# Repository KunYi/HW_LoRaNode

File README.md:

Agritech with LoRa
===
the project want to make an agritech sensor baseboard.

initial version will use RS485 to connection multi-agricultural sensors for precision agriculture management requirments

---
PCB 3D-preview

---
hardward design use [KiCad EDA](https://kicad-pcb.org/)

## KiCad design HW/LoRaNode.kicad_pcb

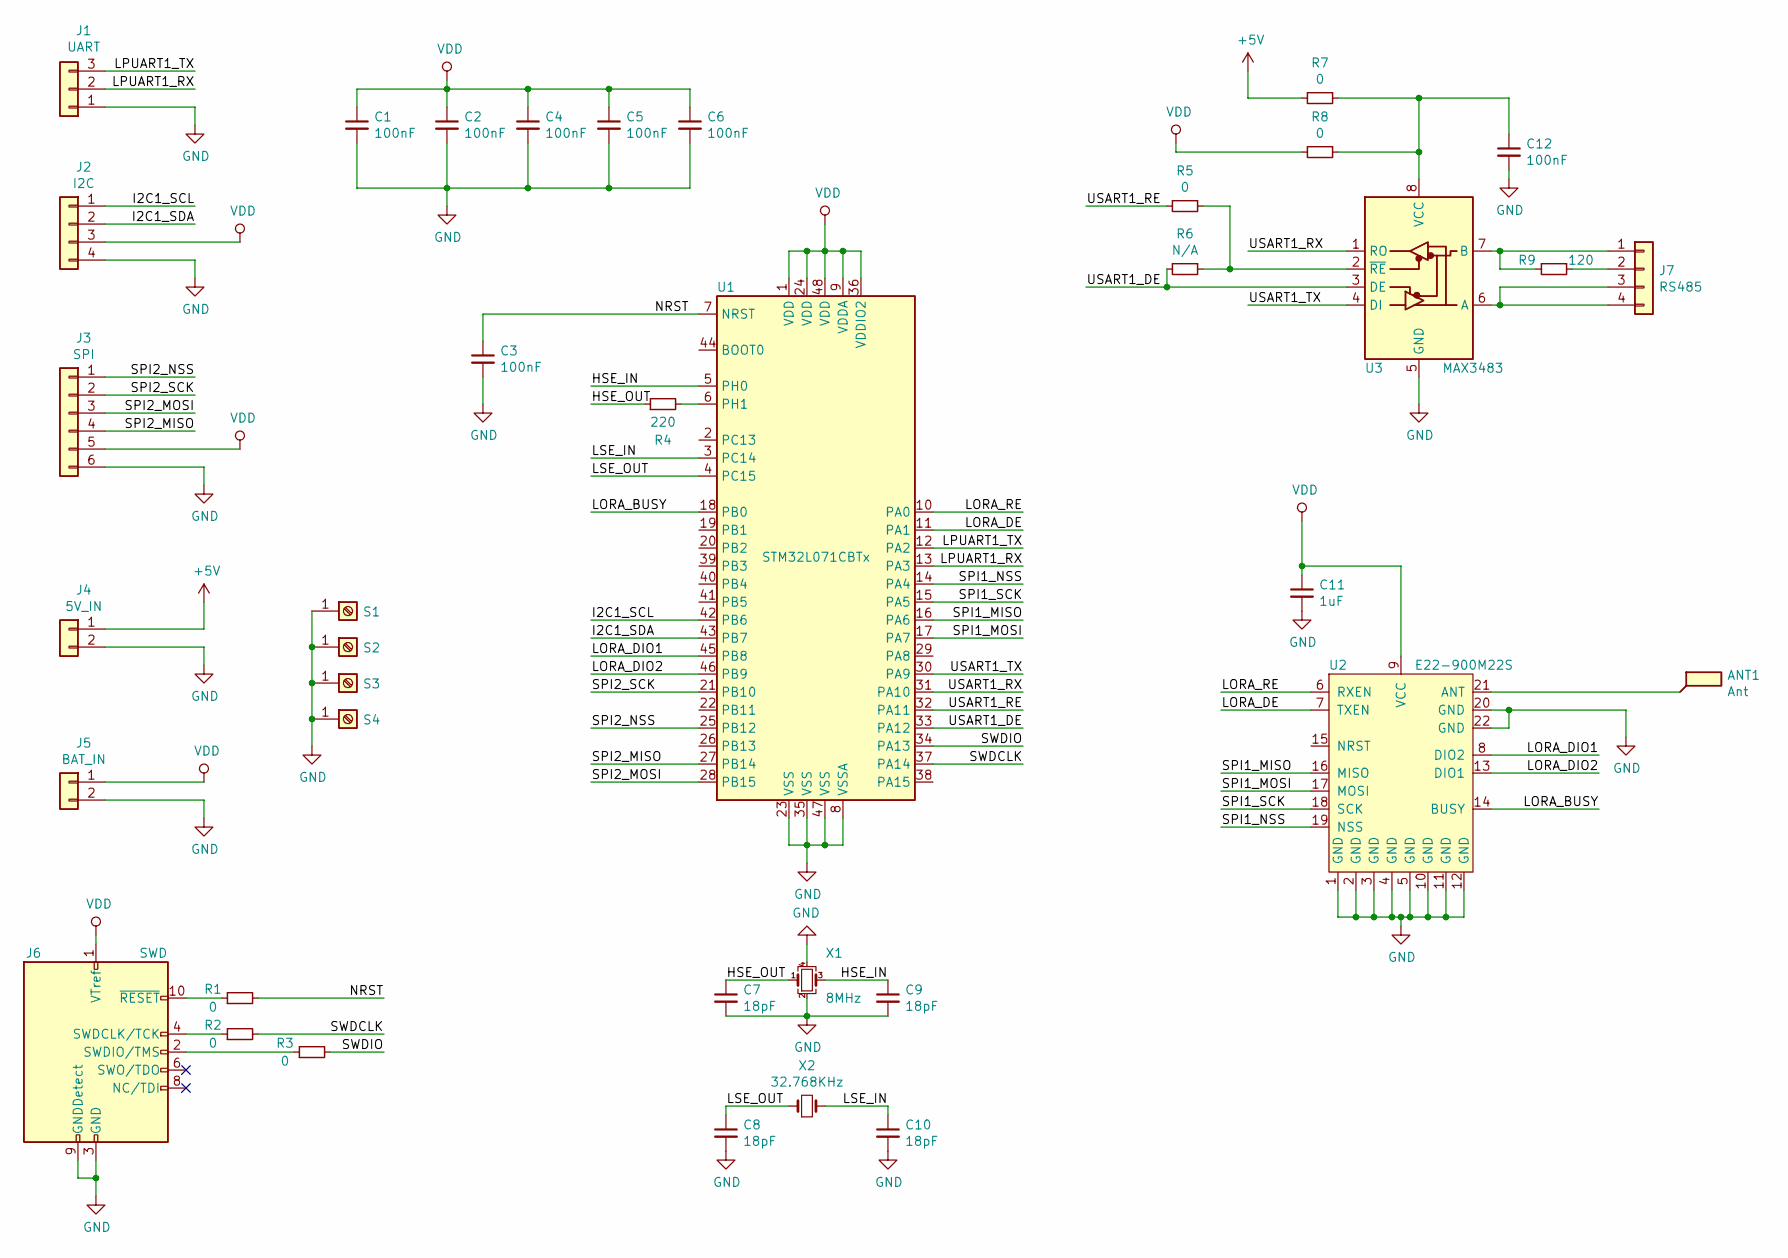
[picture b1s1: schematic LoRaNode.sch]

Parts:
ANT1: Ant; TestPoint_Pad_2.0x2.0mm
C1, C2, C3, C4, C5, C6, C12: 100nF; C_0402_1005Metric
C7, C8, C9, C10: 18pF; C_0402_1005Metric
C11: 1uF; C_0603_1608Metric
J1: UART; PinSocket_1x03_P2.00mm_Vertical
J2: I2C; PinSocket_1x04_P2.00mm_Vertical
J3: SPI; PinSocket_1x06_P2.00mm_Vertical
J4: 5V_IN; PinSocket_1x02_P2.54mm_Vertical
J5: BAT_IN; PinSocket_1x02_P2.54mm_Vertical
J6: SWD; PinHeader_2x05_P1.27mm_Vertical_SMD
J7: RS485; PinHeader_1x04_P2.54mm_Vertical
R1, R2, R3, R5, R7, R8: 0; R_0402_1005Metric
R4: 220; R_0402_1005Metric
R6: N/A; R_0402_1005Metric
R9: 120; R_0603_1608Metric
S1: S1; TestPoint_Plated_Hole_D3.0mm
S2: S2; TestPoint_Plated_Hole_D3.0mm
S3: S3; TestPoint_Plated_Hole_D3.0mm
S4: S4; TestPoint_Plated_Hole_D3.0mm
U1: STM32L071CBTx; LQFP-48_7x7mm_P0.5mm
U2: E22-900M22S; EBYTE-E22-XXXM22S
U3: MAX3483; SO-8_3.9x4.9mm_P1.27mm
X1: 8MHz; Crystal_SMD_TXC_7M-4Pin_3.2x2.5mm
X2: 32.768KHz; Crystal_SMD_3215-2Pin_3.2x1.5mm

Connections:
+5V: J4.1, R7.2
/HSE_IN: C9.1, U1.5 (PH0), X1.3
/HSE_OUT: C7.1, R4.1, X1.1
/I2C1_SCL: J2.1, U1.42 (PB6)
/I2C1_SDA: J2.2, U1.43 (PB7)
/LORA_BUSY: U1.18 (PB0), U2.14 (BUSY)
/LORA_DE: U1.11 (PA1), U2.7 (TXEN)
/LORA_DIO1: U1.45 (PB8), U2.8 (DIO2)
/LORA_DIO2: U1.46 (PB9), U2.13 (DIO1)
/LORA_RE: U1.10 (PA0), U2.6 (RXEN)
/LPUART1_RX: J1.2, U1.13 (PA3)
/LPUART1_TX: J1.3, U1.12 (PA2)
/LSE_IN: C10.1, U1.3 (PC14), X2.2
/LSE_OUT: C8.1, U1.4 (PC15), X2.1
/NRST: C3.1, R1.2, U1.7 (NRST)
/SPI1_MISO: U1.16 (PA6), U2.16 (MISO)
/SPI1_MOSI: U1.17 (PA7), U2.17 (MOSI)
/SPI1_NSS: U1.14 (PA4), U2.19 (NSS)
/SPI1_SCK: U1.15 (PA5), U2.18 (SCK)
/SPI2_MISO: J3.4, U1.27 (PB14)
/SPI2_MOSI: J3.3, U1.28 (PB15)
/SPI2_NSS: J3.1, U1.25 (PB12)
/SPI2_SCK: J3.2, U1.21 (PB10)
/SWDCLK: R2.2, U1.37 (PA14)
/SWDIO: R3.2, U1.34 (PA13)
/USART1_DE: R6.2, U1.33 (PA12), U3.3 (DE)
/USART1_RE: R5.2, U1.32 (PA11)
/USART1_RX: U1.31 (PA10), U3.1 (RO)
/USART1_TX: U1.30 (PA9), U3.4 (DI)
GND: C1.2, C2.2, C3.2, C4.2, C5.2, C6.2, C7.2, C8.2, C9.2, C10.2, C11.2, C12.2, J1.1, J2.4, J3.6, J4.2, J5.2, J6.3 (GND), J6.5 (GND), J6.9 (GNDDetect), S1.1, S2.1, S3.1, S4.1, U1.8 (VSSA), U1.23 (VSS), U1.35 (VSS), U1.47 (VSS), U2.1 (GND), U2.2 (GND), U2.3 (GND), U2.4 (GND), U2.5 (GND), U2.10 (GND), U2.11 (GND), U2.12 (GND), U2.20 (GND), U2.22 (GND), U3.5 (GND), X1.2, X1.4
unnamed: ANT1.1, U2.21 (ANT)
unnamed: C12.1, R7.1, R8.1, U3.8 (VCC)
unnamed: J6.2 (SWDIO/TMS), R3.1
unnamed: J6.4 (SWDCLK/TCK), R2.1
unnamed: J6.10 (~RESET~), R1.1
unnamed: J7.1, R9.2, U3.7 (B)
unnamed: J7.2, R9.1
unnamed: J7.3, J7.4, U3.6 (A)
unnamed: R4.2, U1.6 (PH1)
unnamed: R5.1, R6.1, U3.2 (~RE)
VDD: C1.1, C2.1, C4.1, C5.1, C6.1, C11.1, J2.3, J3.5, J5.1, J6.1 (VTref), R8.2, U1.1 (VDD), U1.9 (VDDA), U1.24 (VDD), U1.36 (VDDIO2), U1.48 (VDD), U2.9 (VCC)

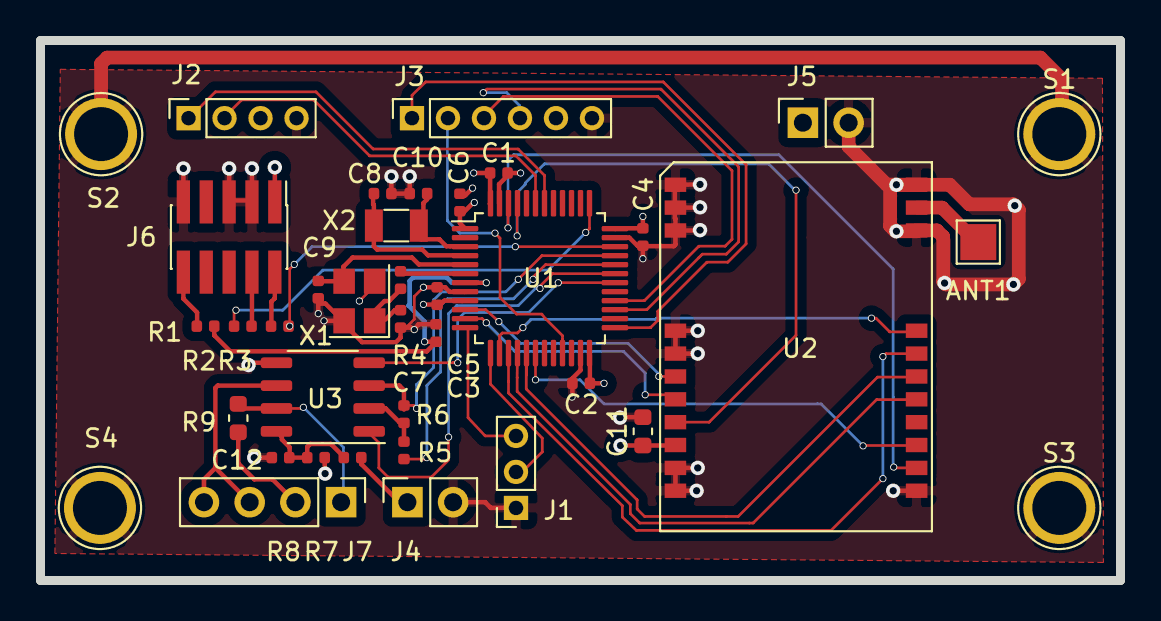
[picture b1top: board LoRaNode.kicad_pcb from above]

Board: 4 copper layers, 60.0 x 30.0 mm, 38 parts (0 on the bottom side), 41 nets.

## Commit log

2020-01-27 Add symbol EByte E22-900M22S into RF_Module
2020-01-27 inital schematic & project files
2020-01-28 rename EBYTE-E22 footprint to EBYTE-E22-XXXM22S
2020-01-28 upload Ebyte E22 series datasheet
2020-01-28 upload more files for this project
2020-01-28 add simple readme
2020-01-28 rename LoRaNoe to HW
2020-01-28 correct path for symbol and footprint
2020-01-28 add cache library of KiCad
2020-01-28 add second source for RS485 transceiver
2020-01-28 update some schematic design
2020-01-29 modify Ebyte E22-XXXM22S footprint
    change pad design for hand made
2020-01-29 add crystal HSE/LSE into schematic
    HSE -- 16MHz for high speed run mode
    LSE -- 32.768KHz for low power mode, LPUART
2020-02-28 update schematic & pcb files for design update
2020-04-12 update schematic
2020-04-12 update project and pcb design
2020-04-12 update PCB and Readme
2020-04-12 update 3d preview
2020-04-18 add lost decouple capacitor
